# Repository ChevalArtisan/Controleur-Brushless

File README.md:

# Controleur-Brushless

Collaborateurs: Hippolyte HANDWERK & Mohamed-Yâ-Sîn MAATI

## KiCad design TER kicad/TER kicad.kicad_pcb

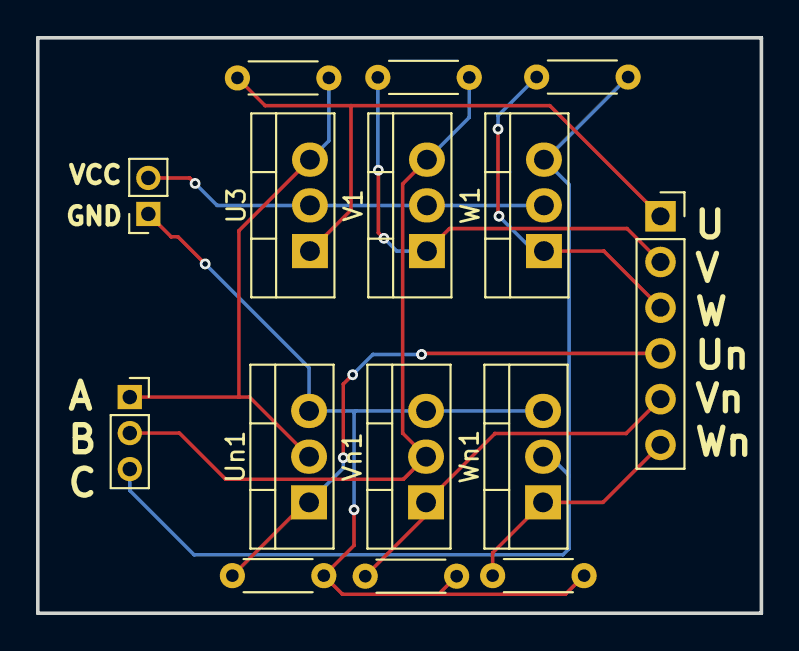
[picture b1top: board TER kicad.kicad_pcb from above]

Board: 2 copper layers, 40.2 x 32.0 mm, 15 parts (0 on the bottom side), 11 nets.

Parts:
J1: Conn_01x06_Pin; PinSocket_1x06_P2.54mm_Vertical
J2: Conn_01x02_Pin; PinSocket_1x02_P2.00mm_Vertical
Mot1: PinSocket_1x03_P2.00mm_Vertical
R1, R2, R3, R4, R5, R6: 10k; R_Axial_DIN0204_L3.6mm_D1.6mm_P5.08mm_Horizontal
U3: MOS; TO-220-3_Vertical
Un1: MOS; TO-220-3_Vertical
V1: MOS; TO-220-3_Vertical
Vn1: MOS; TO-220-3_Vertical
W1: MOS; TO-220-3_Vertical
Wn1: MOS; TO-220-3_Vertical

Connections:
+12V: J2.2, U3.2 (D), V1.2 (D), W1.2 (D)
GND 12V: J2.1, R4.2, R5.2, R6.2, Un1.3 (S), Vn1.3 (S), Wn1.3 (S)
unnamed: J1.1, R1.1, U3.1 (G)
unnamed: J1.4, R4.1, Un1.1 (G)
unnamed: J1.2, R2.1, V1.1 (G)
unnamed: J1.5, R5.1, Vn1.1 (G)
unnamed: J1.3, R3.1, W1.1 (G)
unnamed: J1.6, R6.1, Wn1.1 (G)
unnamed: Mot1.1 (A), R1.2, U3.3 (S), Un1.2 (D)
unnamed: Mot1.2 (B), R2.2, V1.3 (S), Vn1.2 (D)
unnamed: Mot1.3 (C), R3.2, W1.3 (S), Wn1.2 (D)

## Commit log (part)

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2026-05-11 Ajout trad vhdl->verilog
2026-05-19 premier jet
2026-05-21 Feat: add sysverilog v1
2026-05-26 mise sous module de PWM/machine a etat + ajout module controle
2026-05-26 Feat: add test_compte_tour
2026-05-26 Fix : change compte tour logic
2026-05-26 Add .gitignore
2026-05-26 Feat : add test machine a etat
2026-05-26 Feat : add test_pwm_out
2026-05-26 Setup : creation env kicad
2026-05-27 fix module vitesse (tout les modules sont testés et fonctionnels)
2026-06-01 Fix : debug MaE
2026-06-01 Fix : ajout signaux tour
2026-06-01 controleur bldc finis et testé
2026-06-04 fix compteur et ramp en cours
2026-06-05 Fix: current duty compteur vector size and ramp bug
2026-06-05 contoleur bldc terminé
2026-06-10 fix pour synthèse gowin
2026-06-17 Feat: Ajout pyramide (à rendre symetrique)
2026-06-17 Fix: changement pour pyramide
2026-06-17 Fix : Symetrie pyramide
2026-06-26 Maj du kicad
